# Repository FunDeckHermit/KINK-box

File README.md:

# KINK-box

A compact USB-C-powered stereo audio player and amplifier powered by an ESP32-S3 microcontroller.

## Overview

KINK-box is a dedicated audio playback device with built-in amplification, WiFi connectivity, and a simple web interface. Stream audio to speakers or headphones with intuitive physical and web controls.

## Features

- **USB-C Power Delivery**: Powered by standard USB-C PD adapter (12V negotiated)
- **WiFi Connectivity**: Built-in 2.4 GHz WiFi for streaming
- **Web Interface**: Control playback and configuration from any browser
- **Stereo Audio Output**: 
  - Speaker terminals for direct loudspeaker connection
  - 3.5mm line-level jack for headphones or external amplifiers
- **Physical Controls**: 
  - Four RGB-illuminated buttons for quick access
  - Additional tactile button and navigation switch for volume and menu control
- **Class-D Amplifier**: High-efficiency 30W stereo amplifier built-in

## Quick Start

1. **Assembly**: Reference the component placement guide and [Bill of Materials](kicad-artifacts/KINK-box_bom.csv)
2. **Power On**: Connect a USB-C Power Delivery adapter
3. **Connect**: Join the device WiFi network
4. **Access**: Open `http://<device-ip>` in your browser
5. **Play**: Use the web interface or physical buttons to select and play audio
6. **Volume**: Adjust using physical controls or the web interface

## Hardware Files

All manufacturing and design files are in `kicad-artifacts/`:
- **Gerbers**: `KINK-box_gerbers.zip` - For PCB fabrication
- **Schematics**: `KINK-box_schematic.pdf`
- **3D Model**: `KINK-box_board.step`
- **Interactive BOM**: `ibom.html`

## License

Apache License 2.0 - see [LICENSE](LICENSE) for details.

---

**KINK-box** - Simple stereo audio player with built-in amplification and WiFi.

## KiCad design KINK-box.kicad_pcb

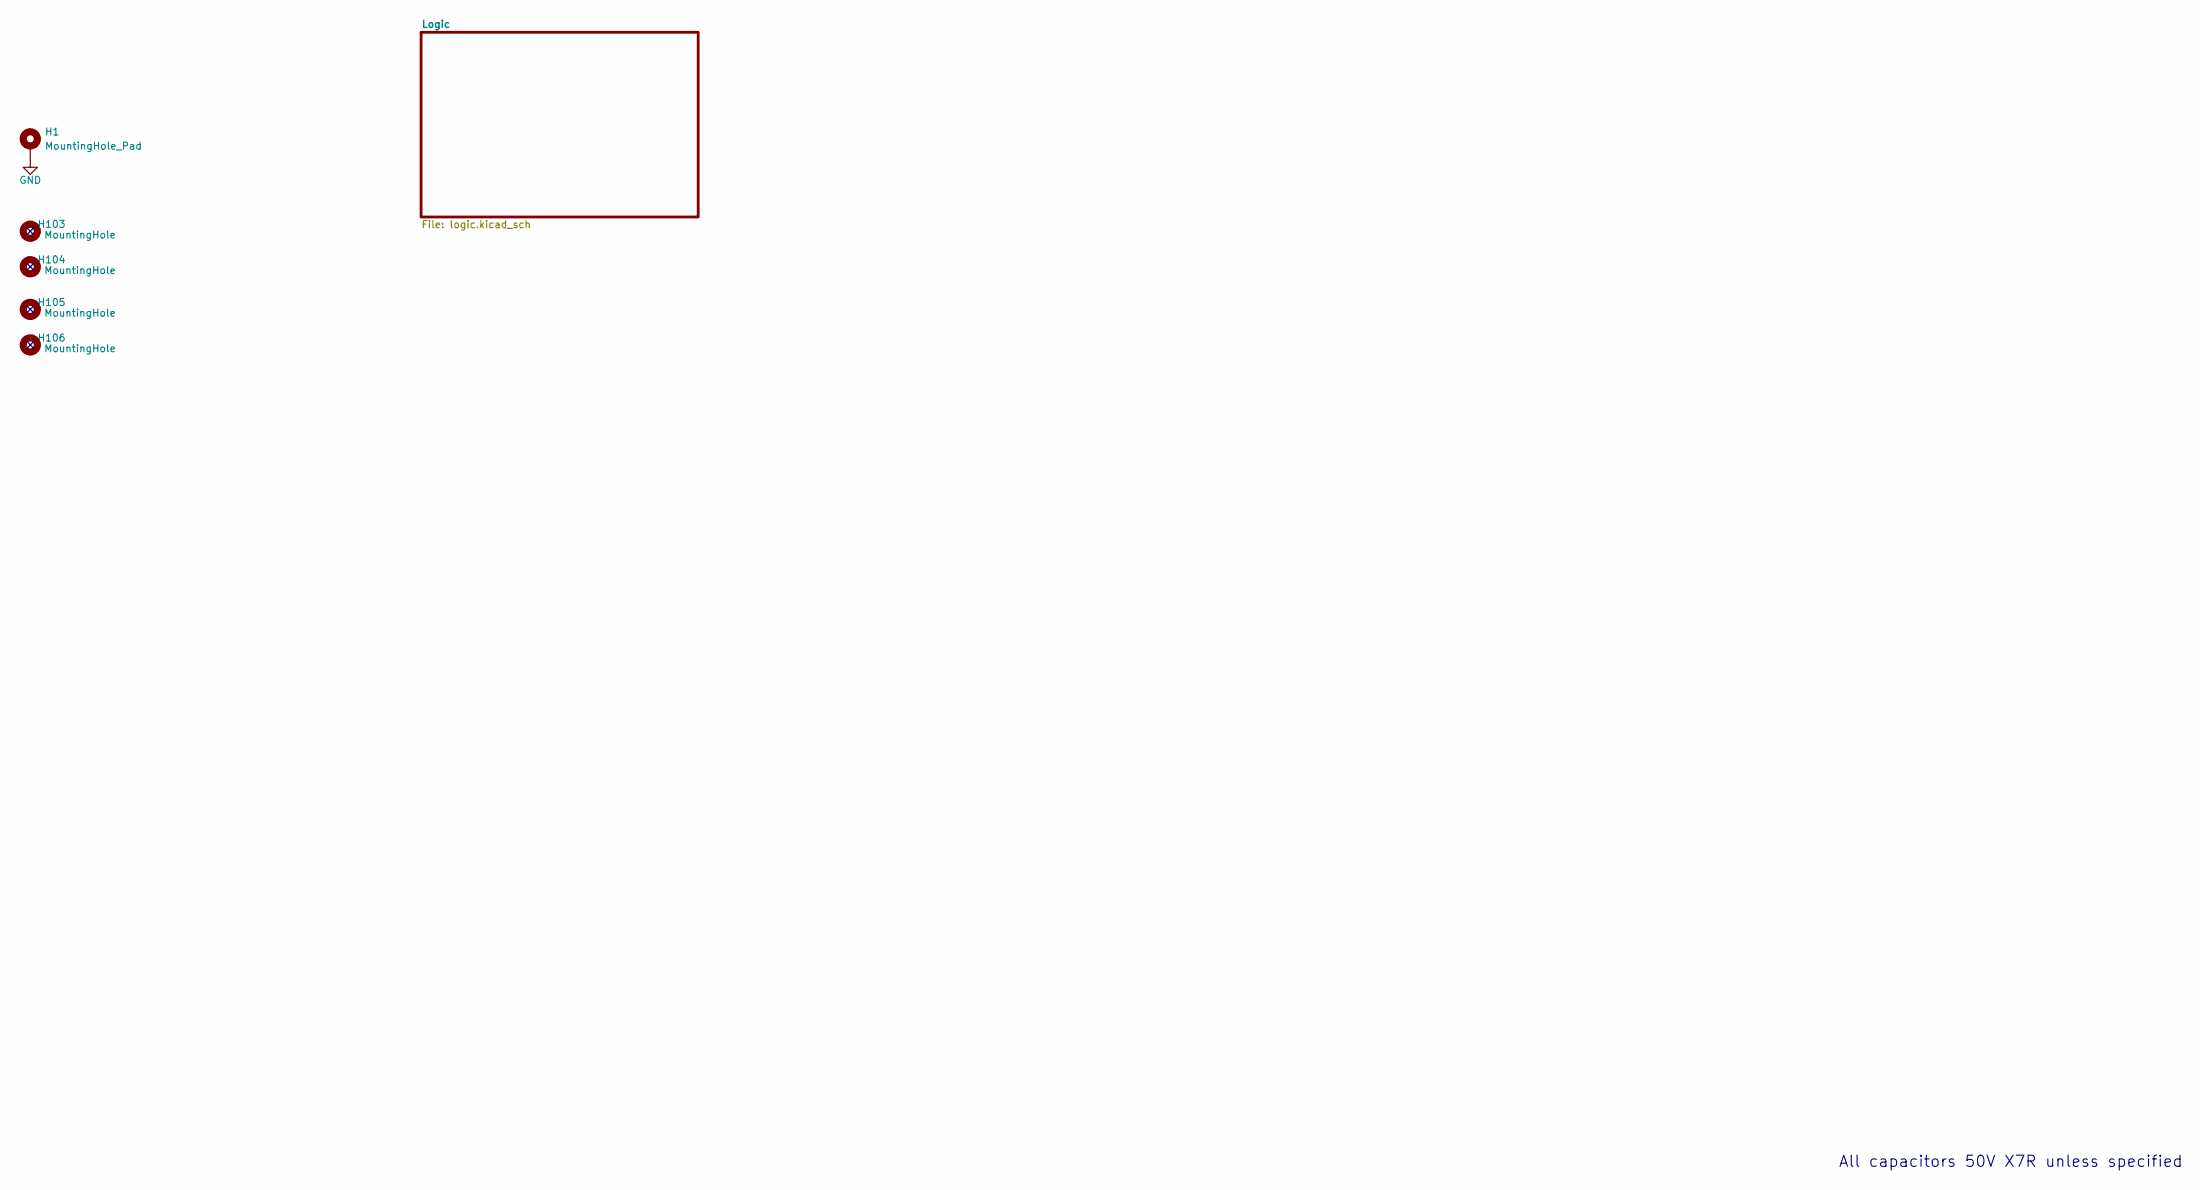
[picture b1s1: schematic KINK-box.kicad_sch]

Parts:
H1: MountingHole_Pad; ESP-solderhole
H103, H104, H105, H106: MountingHole; MountingHole_3.2mm_M3

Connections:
GND: H1.1 (1_1); also elsewhere on the board

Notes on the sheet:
All capacitors 50V X7R unless specified

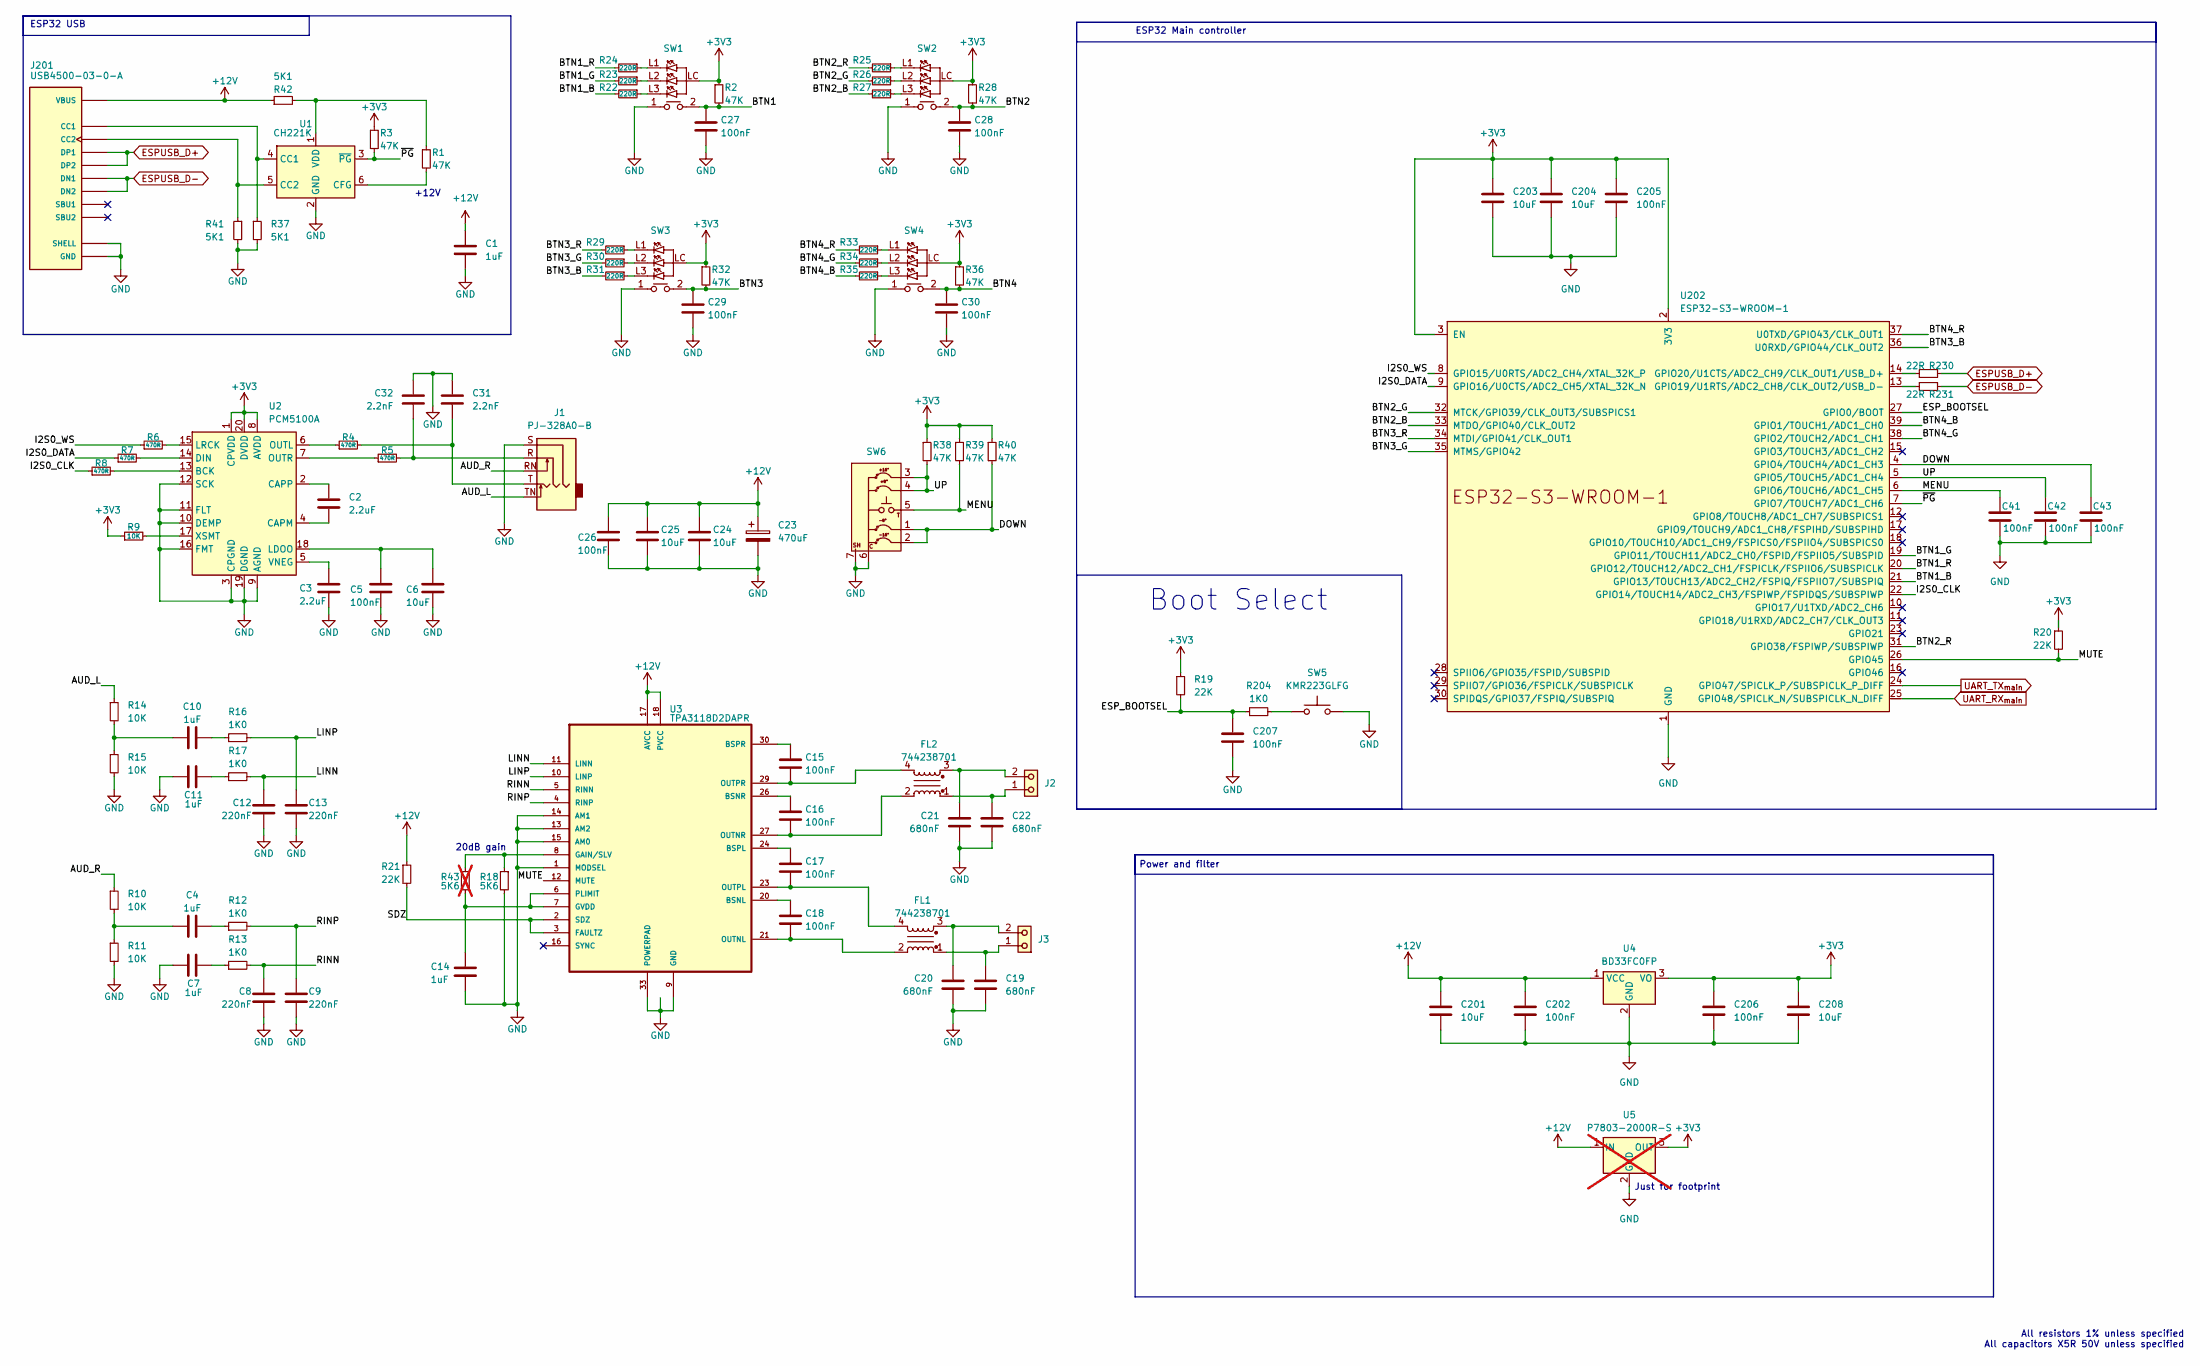
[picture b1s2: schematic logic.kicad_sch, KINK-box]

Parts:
C1, C14: 1uF; C_1206_3216Metric; Rated Voltage 25V; Tolerance ±10%; MPN 1206B105K250CT
C2, C3: 2.2uF; C_0805_2012Metric; Rated Voltage 25V; Tolerance ±10%; MPN 0805B225K250CT
C4, C7, C10, C11: 1uF; C_0603_1608Metric; Rated Voltage 10V; Tolerance ±10%; MPN 0603B105K100CT
C5, C15, C16, C17, C18, C26, C27, C28, C29, C30: 100nF; C_0603_1608Metric; Rated Voltage 50V; Tolerance ±10%; MPN 0603B104K500CT
C6, C201, C208: 10uF; C_1210_3225Metric
C8, C9, C12, C13: 220nF; C_0603_1608Metric; Rated Voltage 50V; Tolerance ±10%; MPN 0603B224K500CT
C19, C20, C21, C22: 680nF; C_0603_1608Metric; Rated Voltage 10V; Tolerance ±10%; MPN 0603B684K100CT
C23: 470uF; CP_Wurth_WCAP-ASLL-D16L17; MPN 865060663013
C24, C25: 10uF; C_1206_3216Metric; Rated Voltage 25V; Tolerance ±10%; MPN 1206B106K250CT
C31, C32: 2.2nF; C_0603_1608Metric; Rated Voltage 50V; Tolerance ±10%; MPN 0603B222K500CT
C41, C42, C43, C202, C205, C206, C207: 100nF; C_0603_1608Metric
C203, C204: 10uF; C_0805_2012Metric
FL1, FL2: 744238701; L_Wurth_WE-CMDC-7060; MPN 744238701
J1: PJ-328A0-B; MPN PJ-328A0-B
J2, J3: QT02CSF83H0000G; MPN QT02CSF83H0000G
J201: USB4500-03-0-A; USB_C_Receptacle_USB4500-03-0-A
R1, R2, R3, R28, R32, R36, R38, R39, R40: 47K; R_0603_1608Metric; MPN RC0603FR-0747KL
R4, R5, R6, R7, R8: 470R; R_0603_1608Metric; MPN RC0603FR-07470RL
R9, R10, R11, R14, R15: 10K; R_0603_1608Metric; MPN RC0603FR-0710KL
R12, R13, R16, R17: 1K0; R_0603_1608Metric; MPN RC0603FR-07FRE131KL
R18: 5K6; R_0603_1608Metric; MPN RC0603FR-075K6L
R19, R20, R21: 22K; R_0603_1608Metric; MPN RC0603FR-0722KL
R22, R23, R24, R25, R26, R27, R29, R30, R31, R33, R34, R35: 220R; R_0603_1608Metric; MPN RC0603FR-07220RL
R37, R41, R42: 5K1; R_0603_1608Metric; MPN RC0603FR-075K1L
R43: 5K6; R_0603_1608Metric; MPN RC0603FR-075K6L; not fitted
R204: 1K0; R_0603_1608Metric
R230, R231: 22R; R_0603_1608Metric
SW1, SW2, SW3, SW4: 465M111172501; SW_Wurth_WS-PBTL_465M111172501; Part Number 465M111172501
SW5: KMR223GLFG; SW_Push_1P1T_NO_CK_KMR2; MPN KMR223GLFG
SW6: SW_PLMG5-GH; MPN PLMG5-GH-V-T/R
U1: CH221K; SOT-23-6
U2: PCM5100A; TSSOP-20_4.4x6.5mm_P0.65mm
U3: TPA3118D2DAPR; HTSSOP-32-1EP_6.1x11mm_P0.65mm_EP5.2x11mm_Mask4.11x4.36mm; MPN TPA3118D2DAPR
U4: BD33FC0FP; TO-252-2; MPN BD33FC0FP-E2
U5: P7803-2000R-S; Converter_DCDC_RECOM_R-78HB-0.5L_THT; MPN P7805-2000R-S; not fitted
U202: ESP32-S3-WROOM-1

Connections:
+3V3: C203.1, C204.1, C205.1, C206.1, C208.1, R2.1, R3.1, R9.1, R19.1, R20.1, R28.1, R32.1, R36.1, R38.1, R39.1, R40.1, SW1.LC, SW2.LC, SW3.LC, SW4.LC, U2.1 (CPVDD), U2.8 (AVDD), U2.20 (DVDD), U4.3 (VO), U5.3 (OUT), U202.2 (3V3), U202.3 (EN)
+12V: C1.1, C23.1, C24.1, C25.1, C26.1, C201.1, C202.1, J201.A4 (VBUS), J201.A9 (VBUS), J201.B4 (VBUS), J201.B9 (VBUS), R21.1, R42.1, U3.17 (AVCC), U3.18 (PVCC), U3.19 (PVCC), U3.31 (PVCC), U3.32 (PVCC), U4.1 (VCC), U5.1 (IN)
/Logic/AUD_L: J1.TN, R14.1
/Logic/AUD_R: J1.RN, R10.1
/Logic/BTN1: C27.1, R2.2, SW1.2
/Logic/BTN1_B: R22.2, U202.21 (GPIO13/TOUCH13/ADC2_CH2/FSPIQ/FSPIIO7/S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)
/Logic/BTN1_G: R23.2, U202.19 (GPIO11/TOUCH11/ADC2_CH0/FSPID/FSPIIO5/S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)
/Logic/BTN1_R: R24.2, U202.20 (GPIO12/TOUCH12/ADC2_CH1/FSPICLK/FSPIIO6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)
/Logic/BTN2: C28.1, R28.2, SW2.2
/Logic/BTN2_B: R27.2, U202.33 (MTDO/GPIO40/CLK_OUT2)
/Logic/BTN2_G: R26.2, U202.32 (MTCK/GPIO39/CLK_OUT3/SUBSPICS1)
/Logic/BTN2_R: R25.2, U202.31 (GPIO38/FSPIWP/SUBSPIWP)
/Logic/BTN3: C29.1, R32.2, SW3.2
/Logic/BTN3_B: R31.2, U202.36 (U0RXD/GPIO44/CLK_OUT2)
/Logic/BTN3_G: R30.2, U202.35 (MTMS/GPIO42)
/Logic/BTN3_R: R29.2, U202.34 (MTDI/GPIO41/CLK_OUT1)
/Logic/BTN4: C30.1, R36.2, SW4.2
/Logic/BTN4_B: R35.2, U202.39 (GPIO1/TOUCH1/ADC1_CH0)
/Logic/BTN4_G: R34.2, U202.38 (GPIO2/TOUCH2/ADC1_CH1)
/Logic/BTN4_R: R33.2, U202.37 (U0TXD/GPIO43/CLK_OUT1)
/Logic/DOWN: C43.1, R40.2, SW6.1, SW6.2, U202.4 (GPIO4/TOUCH4/ADC1_CH3)
/Logic/ESP_BOOTSEL: C207.1, R19.2, R204.1, U202.27 (GPIO0/BOOT)
/Logic/I2S0_CLK: R8.1, U202.22 (GPIO14/TOUCH14/ADC2_CH3/FSPIWP/FSPIDQS/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)
/Logic/I2S0_DATA: R7.1, U202.9 (GPIO16/U0CTS/ADC2_CH5/XTAL_32K_N)
/Logic/I2S0_WS: R6.1, U202.8 (GPIO15/U0RTS/ADC2_CH4/XTAL_32K_P)
/Logic/LINN: C12.1, R17.2, U3.11 (LINN)
/Logic/LINP: C13.1, R16.2, U3.10 (LINP)
/Logic/MENU: C41.1, R39.2, SW6.5, U202.6 (GPIO6/TOUCH6/ADC1_CH5)
/Logic/MUTE: R20.2, U3.12 (MUTE), U202.26 (GPIO45)
/Logic/RINN: C8.1, R13.2, U3.5 (RINN)
/Logic/RINP: C9.1, R12.2, U3.4 (RINP)
/Logic/SDZ: R21.2, U3.2 (SDZ), U3.3 (FAULTZ)
/Logic/UP: C42.1, R38.2, SW6.3, SW6.4, U202.5 (GPIO5/TOUCH5/ADC1_CH4)
/Logic/~PG: R3.2, U1.3 (~PG), U202.7 (GPIO7/TOUCH7/ADC1_CH6)
ESPUSB_D+: J201.A6 (DP1), J201.B6 (DP2), R230.2
ESPUSB_D-: J201.A7 (DN1), J201.B7 (DN2), R231.2
GND: C1.2, C3.2, C5.2, C6.2, C7.1, C8.2, C9.2, C11.1, C12.2, C13.2, C14.2, C19.2, C20.2, C21.2, C22.2, C23.2, C24.2, C25.2, C26.2, C27.2, C28.2, C29.2, C30.2, C31.1, C32.1, C41.2, C42.2, C43.2, C201.2, C202.2, C203.2, C204.2, C205.2, C206.2, C207.2, C208.2, J1.S, J201.A1 (GND), J201.A12 (GND), J201.B1 (GND), J201.B12 (GND), J201.S1 (SHELL), R11.2, R15.2, R18.2, R37.2, R41.2, SW1.1, SW2.1, SW3.1, SW4.1, SW5.2, SW6.6, SW6.7, U1.2 (GND), U2.3 (CPGND), U2.9 (AGND), U2.10 (DEMP), U2.11 (FLT), U2.12 (SCK), U2.16 (FMT), U2.19 (DGND), U3.1 (MODSEL), U3.9 (GND), U3.13 (AM2), U3.14 (AM1), U3.15 (AM0), U3.22 (GND), U3.25 (GND), U3.28 (GND), U3.33 (POWERPAD), U4.2 (GND), U5.2 (GND), U202.1 (GND), U202.40 (GND), U202.41 (GND); also elsewhere on the board
unnamed: C4.1, R10.2, R11.1
unnamed: C4.2, R12.1
unnamed: C7.2, R13.1
unnamed: C10.1, R14.2, R15.1
unnamed: C10.2, R16.1
unnamed: C11.2, R17.1
unnamed: C19.1, FL1.1, J3.1
unnamed: C20.1, FL1.3, J3.2
unnamed: C21.1, FL2.3, J2.2
unnamed: C22.1, FL2.1, J2.1
unnamed: C31.2, J1.T, R4.2
unnamed: C32.2, J1.R, R5.2
unnamed: J201.A5 (CC1), R37.1, U1.4 (CC1)
unnamed: J201.B5 (CC2), R41.1, U1.5 (CC2)
unnamed: R204.2, SW5.1
unnamed: R22.1, SW1.L3 (BLUE)
unnamed: R23.1, SW1.L2 (GREEN)
unnamed: R24.1, SW1.L1 (RED)
unnamed: R27.1, SW2.L3 (BLUE)
unnamed: R26.1, SW2.L2 (GREEN)
unnamed: R25.1, SW2.L1 (RED)
unnamed: R31.1, SW3.L3 (BLUE)
unnamed: R30.1, SW3.L2 (GREEN)
unnamed: R29.1, SW3.L1 (RED)
unnamed: R35.1, SW4.L3 (BLUE)
unnamed: R34.1, SW4.L2 (GREEN)
unnamed: R33.1, SW4.L1 (RED)
unnamed: R1.2, U1.6 (CFG)
unnamed: R1.1, R42.2, U1.1 (VDD)
unnamed: R8.2, U2.13 (BCK)
unnamed: C2.2, U2.4 (CAPM)
unnamed: C2.1, U2.2 (CAPP)
unnamed: R7.2, U2.14 (DIN)
unnamed: C5.1, C6.1, U2.18 (LDOO)
unnamed: R6.2, U2.15 (LRCK)
unnamed: R4.1, U2.6 (OUTL)
unnamed: R5.1, U2.7 (OUTR)
unnamed: C3.1, U2.5 (VNEG)
unnamed: R9.2, U2.17 (XSMT)
unnamed: C18.1, U3.20 (BSNL)
unnamed: C16.1, U3.26 (BSNR)
unnamed: C17.1, U3.24 (BSPL)
unnamed: C15.1, U3.30 (BSPR)
unnamed: R18.1, R43.1, U3.8 (GAIN/SLV)
unnamed: C14.1, R43.2, U3.6 (PLIMIT), U3.7 (GVDD)
unnamed: C18.2, FL1.2, U3.21 (OUTNL)
unnamed: C16.2, FL2.2, U3.27 (OUTNR)
unnamed: C17.2, FL1.4, U3.23 (OUTPL)
unnamed: C15.2, FL2.4, U3.29 (OUTPR)
unnamed: R231.1, U202.13 (GPIO19/U1RTS/ADC2_CH8/CLK_OUT2/USB_D-)
unnamed: R230.1, U202.14 (GPIO20/U1CTS/ADC2_CH9/CLK_OUT1/USB_D+)
UART_RX_{main}: U202.25 (GPIO48/SPICLK_N/SUBSPICLK_N_DIFF)
UART_TX_{main}: U202.24 (GPIO47/SPICLK_P/SUBSPICLK_P_DIFF)

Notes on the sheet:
+12V
ESP32 USB
Power and filter
20dB gain
All resistors 1% unless specified All capacitors X5R 50V unless specified
Just for footprint
Boot Select
ESP32 Main controller

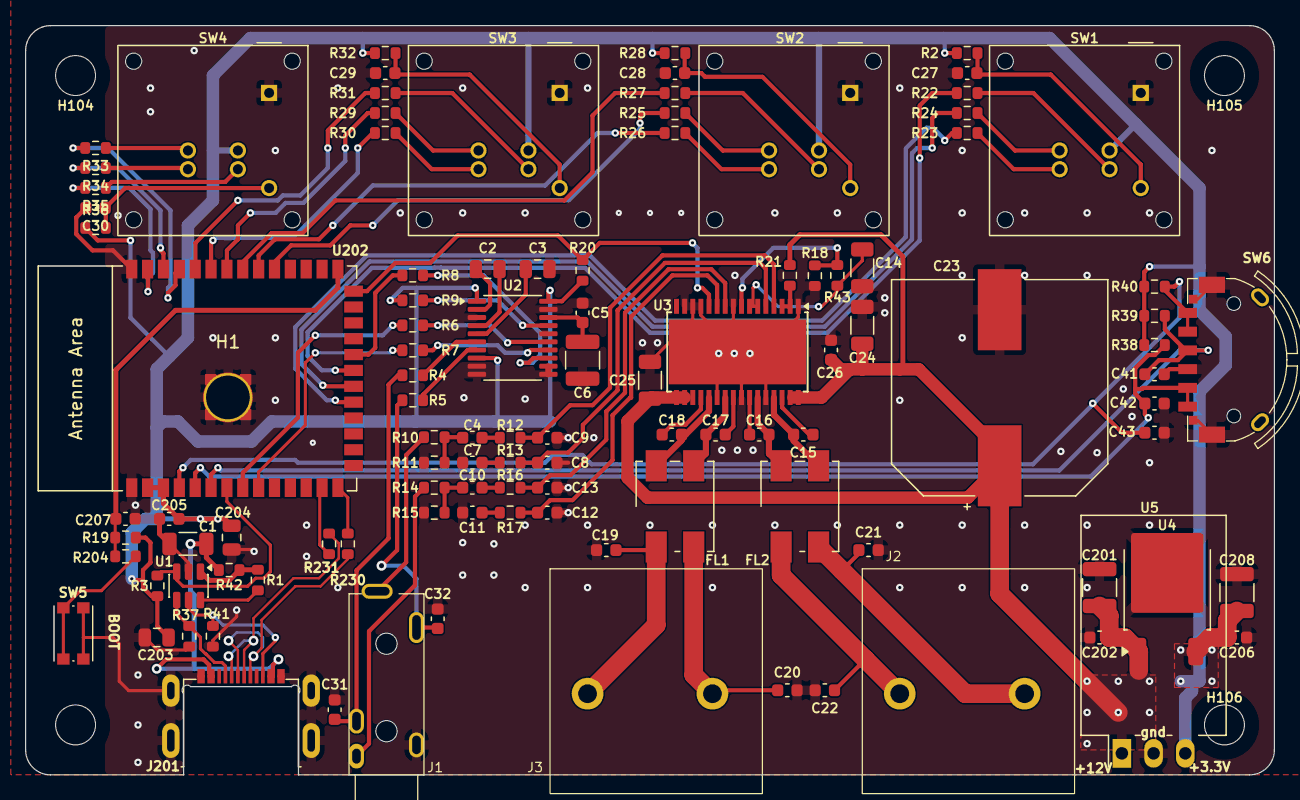
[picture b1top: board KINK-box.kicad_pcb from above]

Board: 2 copper layers, 100.0 x 60.0 mm, 112 parts (0 on the bottom side), 88 nets.

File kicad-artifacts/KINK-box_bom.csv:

"Designator"," Comment"," MPN"," Footprint"," Quantity"
"C1,C4,C7,C10,C11,C14","1uF","0603B105K100CT,1206B105K250CT","Capacitor_SMD:C_0603_1608Metric,Capacitor_SMD:C_1206_3216Metric","6"
"C2,C3","2.2uF","0805B225K250CT","Capacitor_SMD:C_0805_2012Metric","2"
"C5,C15,C16,C17,C18,C26,C27,C28,C29,C30,C41,C42,C43,C202,C205,C206,C207","100nF","0603B104K500CT","Capacitor_SMD:C_0603_1608Metric","17"
"C6,C24,C25,C201,C203,C204,C208","10uF","1206B106K250CT","Capacitor_SMD:C_0805_2012Metric,Capacitor_SMD:C_1206_3216Metric,Capacitor_SMD:C_1210_3225Metric","7"
"C8,C9,C12,C13","220nF","0603B224K500CT","Capacitor_SMD:C_0603_1608Metric","4"
"C19,C20,C21,C22","680nF","0603B684K100CT","Capacitor_SMD:C_0603_1608Metric","4"
"C23","470uF","865060663013","0_NRD_footprints:CP_Wurth_WCAP-ASLL-D16L17","1"
"C31,C32","2.2nF","0603B222K500CT","Capacitor_SMD:C_0603_1608Metric","2"
"FL1,FL2","744238701","744238701","0_NRD_footprints:L_Wurth_WE-CMDC-7060","2"
"H103,H104,H105,H106","MountingHole","","MountingHole:MountingHole_3.2mm_M3","4"
"J1","PJ-328A0-B","PJ-328A0-B","0_NRD_footprints:PJ-328A0-B","1"
"J2,J3","QT02CSF83H0000G","QT02CSF83H0000G","0_NRD_footprints:QT02CSF83H0000G","2"
"J201","USB4500-03-0-A","","_projectlib:USB_C_Receptacle_USB4500-03-0-A","1"
"R1,R2,R3,R28,R32,R36,R38,R39,R40","47K","RC0603FR-0747KL","Resistor_SMD:R_0603_1608Metric","9"
"R4,R5,R6,R7,R8","470R","RC0603FR-07470RL","Resistor_SMD:R_0603_1608Metric","5"
"R9,R10,R11,R14,R15","10K","RC0603FR-0710KL","Resistor_SMD:R_0603_1608Metric","5"
"R12,R13,R16,R17,R204","1K0","RC0603FR-07FRE131KL","Resistor_SMD:R_0603_1608Metric","5"
"R18","5K6","RC0603FR-075K6L","Resistor_SMD:R_0603_1608Metric","1"
"R19,R20,R21","22K","RC0603FR-0722KL","Resistor_SMD:R_0603_1608Metric","3"
"R22,R23,R24,R25,R26,R27,R29,R30,R31,R33,R34,R35","220R","RC0603FR-07220RL","Resistor_SMD:R_0603_1608Metric","12"
"R37,R41,R42","5K1","RC0603FR-075K1L","Resistor_SMD:R_0603_1608Metric","3"
"R230,R231","22R","","Resistor_SMD:R_0603_1608Metric","2"
"SW1,SW2,SW3,SW4","465M111172501","","0_NRD_footprints:SW_Wurth_WS-PBTL_465M111172501","4"
"SW5","KMR223GLFG","KMR223GLFG","0_NRD_footprints:SW_Push_1P1T_NO_CK_KMR2","1"
"SW6","","PLMG5-GH-V-T/R ","0_NRD_footprints:SW_PLMG5-GH","1"
"U1","CH221K","","Package_TO_SOT_SMD:SOT-23-6","1"
"U2","PCM5100A","","Package_SO:TSSOP-20_4.4x6.5mm_P0.65mm","1"
"U3","TPA3118D2DAPR","TPA3118D2DAPR","Package_SO:HTSSOP-32-1EP_6.1x11mm_P0.65mm_EP5.2x11mm_Mask4.11x4.36mm","1"
"U4","BD33FC0FP","BD33FC0FP-E2","Package_TO_SOT_SMD:TO-252-2","1"
"U202","ESP32-S3-WROOM-1","","_projectlib:ESP32-S3-WROOM-1","1"
